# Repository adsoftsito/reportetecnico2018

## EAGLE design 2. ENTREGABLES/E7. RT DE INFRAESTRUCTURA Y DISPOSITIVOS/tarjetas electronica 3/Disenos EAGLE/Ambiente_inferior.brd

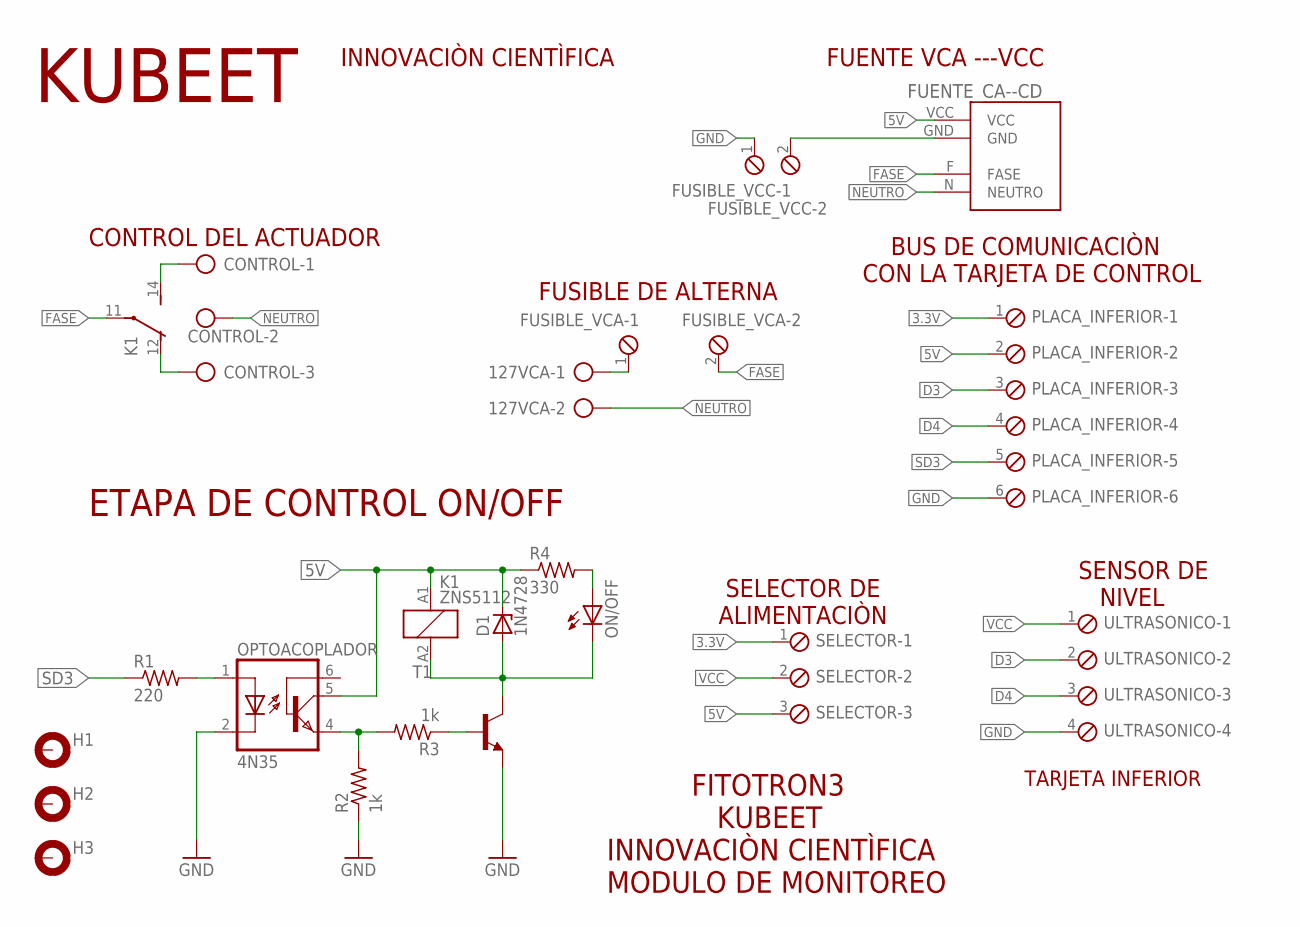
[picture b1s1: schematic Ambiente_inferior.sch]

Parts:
127VCA: AK300/2
CONTROL: AK300/3
D1: 1N4728; DO41Z10
FUENTE_CA--CD: MINI-FUENTE
FUSIBLE_VCA: MPT2; 2POL254
FUSIBLE_VCC: MPT2; 2POL254
H1, H2, H3: MOUNT-PAD-ROUND3.6; 3,6-PAD
K1: ZNS5112; ZN5
ON/OFF: LED5MM
OPTOACOPLADOR: 4N35; DIL06
PLACA_INFERIOR: MPT6; 6POL254
R1: 220; 0207/7
R2, R3: 1k; 0207/7
R4: 330; 0207/7
SELECTOR: MPT3; 3POL254
T1: 2N2222-NPN-TO92-EBC; TO92-EBC
ULTRASONICO: MPT4; 4POL254

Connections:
3.3V: PLACA_INFERIOR.1, SELECTOR.1
5V: D1.C, FUENTE_CA--CD.VCC, K1.A1 (1), OPTOACOPLADOR.5 (COL), PLACA_INFERIOR.2, R4.1, SELECTOR.3
D3: PLACA_INFERIOR.3, ULTRASONICO.2
D4: PLACA_INFERIOR.4, ULTRASONICO.3
FASE: FUENTE_CA--CD.F (FASE), FUSIBLE_VCA.2, K1.11
GND: FUSIBLE_VCC.1, OPTOACOPLADOR.2 (C), PLACA_INFERIOR.6, R2.1, T1.E, ULTRASONICO.4
unnamed: OPTOACOPLADOR.1 (A), R1.2
unnamed: D1.A, K1.A2 (2), ON/OFF.K (C), T1.C
unnamed: OPTOACOPLADOR.4 (EMI), R2.2, R3.2
unnamed: CONTROL.1, K1.14 (S)
unnamed: CONTROL.3, K1.12 (O)
unnamed: 127VCA.1, FUSIBLE_VCA.1
unnamed: R3.1, T1.B
unnamed: ON/OFF.A, R4.2
unnamed: FUENTE_CA--CD.GND, FUSIBLE_VCC.2
NEUTRO: 127VCA.2, CONTROL.2, FUENTE_CA--CD.N (NEUTRO)
SD3: PLACA_INFERIOR.5, R1.1
VCC: SELECTOR.2, ULTRASONICO.1

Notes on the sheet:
FITOTRON3 KUBEET INNOVACIÒN CIENTÌFICA MODULO DE MONITOREO
TARJETA INFERIOR
ETAPA DE CONTROL ON/OFF
FUENTE VCA ---VCC
FUSIBLE DE ALTERNA
CONTROL DEL ACTUADOR
BUS DE COMUNICACIÒN CON LA TARJETA DE CONTROL
SELECTOR DE ALIMENTACIÒN
SENSOR DE NIVEL
KUBEET
INNOVACIÒN CIENTÌFICA

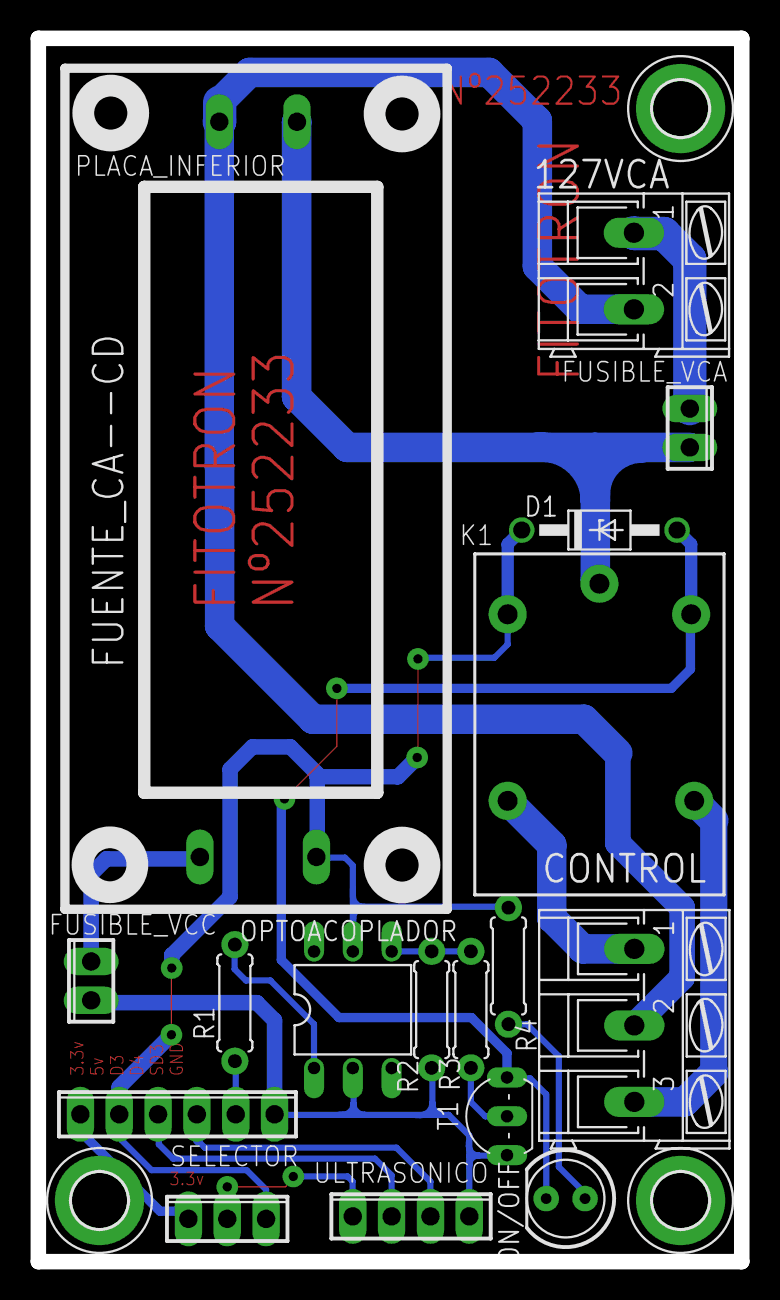
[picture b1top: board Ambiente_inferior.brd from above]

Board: 2 copper layers, 46.0 x 80.0 mm, 20 parts (0 on the bottom side), 18 nets.

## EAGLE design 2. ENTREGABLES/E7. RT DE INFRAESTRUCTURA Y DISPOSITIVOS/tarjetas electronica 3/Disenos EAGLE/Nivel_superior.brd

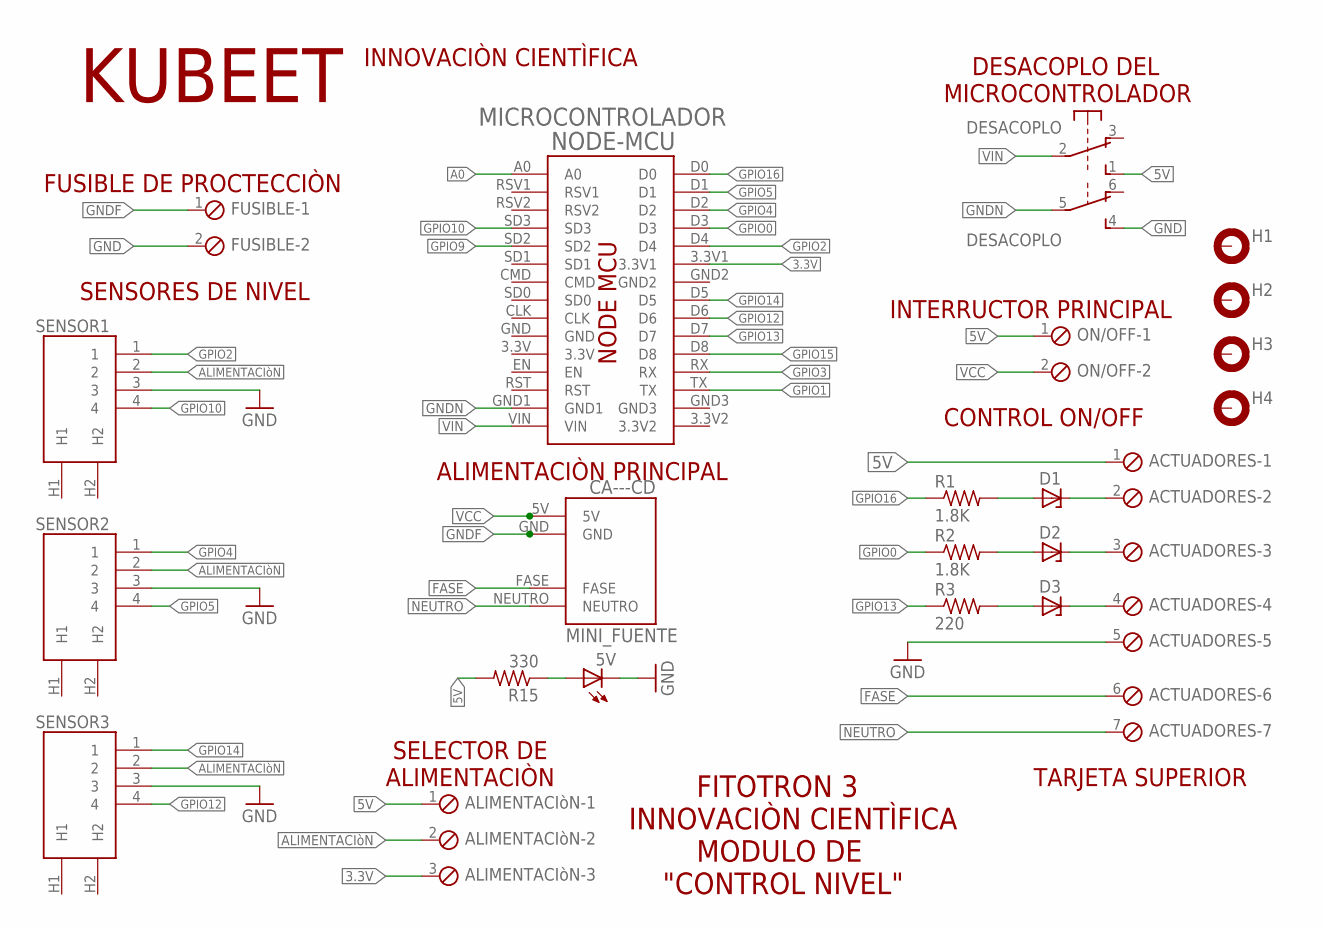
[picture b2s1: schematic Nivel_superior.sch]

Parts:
5V: LED5MM
ACTUADORES: MPT7; 7POL254
ALIMENTACIòN: MPT3; 3POL254
CA---CD: MINI_FUENTE; MINI_FUENTE2
D1, D2, D3: 1N821; DO35Z10
DESACOPLO: 9077-2
FUSIBLE: MPT2; 2POL254
H1, H2, H3, H4: MOUNT-PAD-ROUND3.6; 3,6-PAD
MICROCONTROLADOR: NODE-MCU
ON/OFF: MPT2; 2POL254
R1, R2: 1.8K; 0207/7
R3: 220; 0207/7
R15: 330; 0207/7
SENSOR1, SENSOR2, SENSOR3: RJ11

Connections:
3.3V: ALIMENTACIòN.3, MICROCONTROLADOR.3.3V1
5V: ACTUADORES.1, ALIMENTACIòN.1, DESACOPLO.1 (S), ON/OFF.1, R15.2
A0: MICROCONTROLADOR.A0
ALIMENTACIòN: ALIMENTACIòN.2, SENSOR1.2, SENSOR2.2, SENSOR3.2
FASE: ACTUADORES.6, CA---CD.FASE
GND: 5V.K (C), ACTUADORES.5, DESACOPLO.4 (S), FUSIBLE.2, SENSOR1.3, SENSOR2.3, SENSOR3.3
GNDF: CA---CD.GND, FUSIBLE.1
GNDN: DESACOPLO.5, MICROCONTROLADOR.GND1
GPIO0: MICROCONTROLADOR.D3, R2.1
GPIO1: MICROCONTROLADOR.TX
GPIO2: MICROCONTROLADOR.D4, SENSOR1.1
GPIO3: MICROCONTROLADOR.RX
GPIO4: MICROCONTROLADOR.D2, SENSOR2.1
GPIO5: MICROCONTROLADOR.D1, SENSOR2.4
GPIO9: MICROCONTROLADOR.SD2
GPIO10: MICROCONTROLADOR.SD3, SENSOR1.4
GPIO12: MICROCONTROLADOR.D6, SENSOR3.4
GPIO13: MICROCONTROLADOR.D7, R3.1
GPIO14: MICROCONTROLADOR.D5, SENSOR3.1
GPIO15: MICROCONTROLADOR.D8
GPIO16: MICROCONTROLADOR.D0, R1.1
unnamed: D1.A, R1.2
unnamed: ACTUADORES.2, D1.C
unnamed: D2.A, R2.2
unnamed: ACTUADORES.3, D2.C
unnamed: 5V.A, R15.1
unnamed: D3.A, R3.2
unnamed: ACTUADORES.4, D3.C
NEUTRO: ACTUADORES.7, CA---CD.NEUTRO
VCC: CA---CD.5V, ON/OFF.2
VIN: DESACOPLO.2, MICROCONTROLADOR.VIN

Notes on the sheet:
KUBEET
INNOVACIÒN CIENTÌFICA
FITOTRON 3 INNOVACIÒN CIENTÌFICA MODULO DE "CONTROL NIVEL"
TARJETA SUPERIOR
CONTROL ON/OFF
SENSORES DE NIVEL
DESACOPLO DEL MICROCONTROLADOR
ALIMENTACIÒN PRINCIPAL
SELECTOR DE ALIMENTACIÒN
INTERRUCTOR PRINCIPAL
FUSIBLE DE PROCTECCIÒN

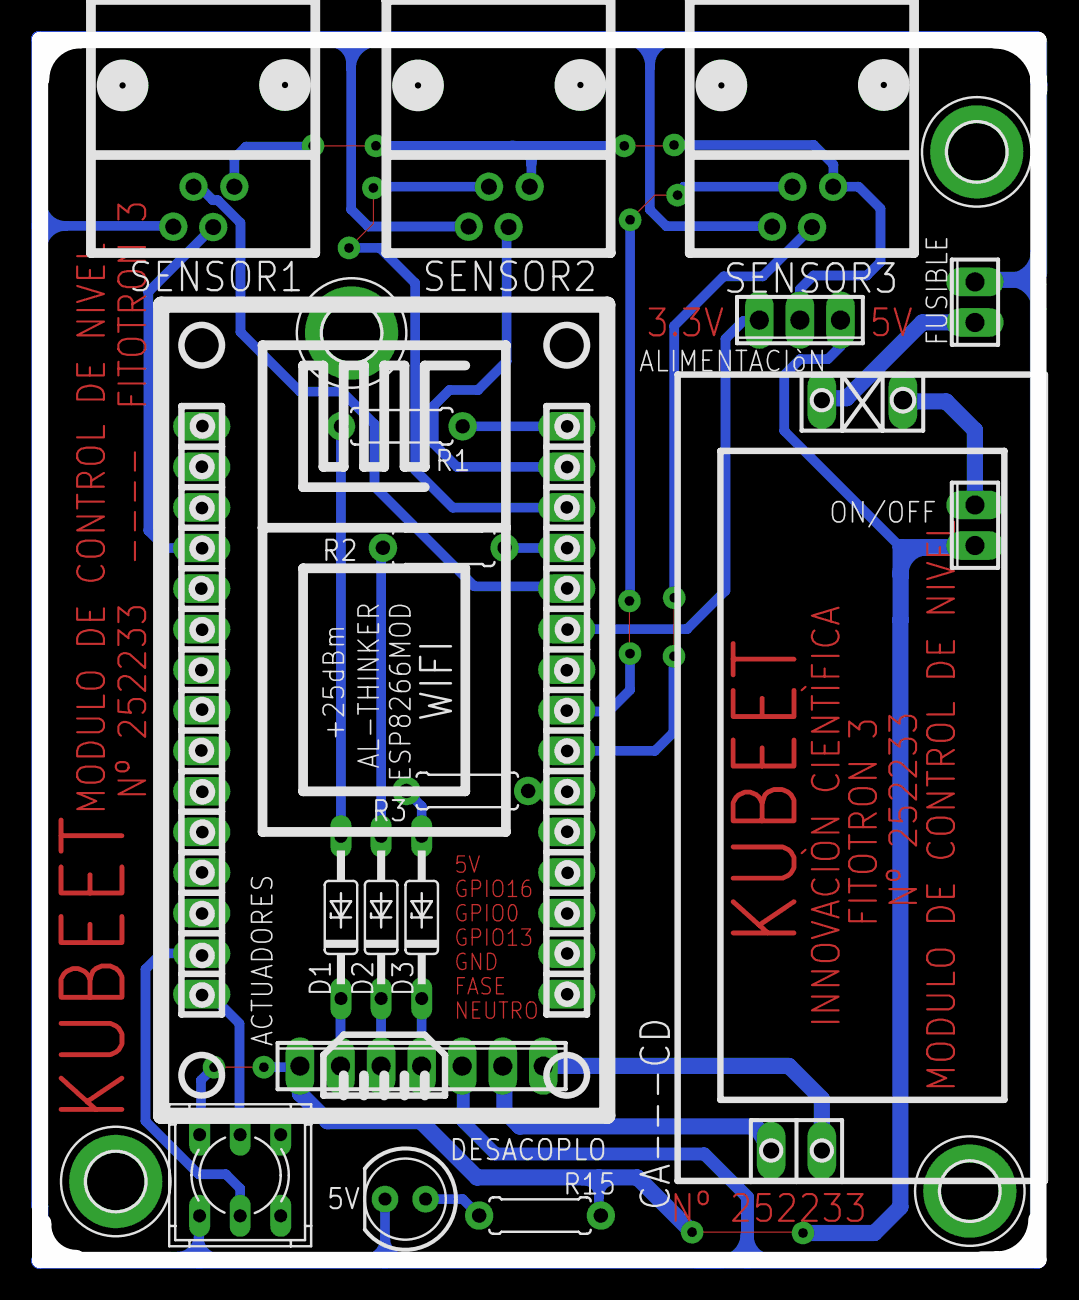
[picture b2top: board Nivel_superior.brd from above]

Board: 2 copper layers, 62.6 x 76.4 mm, 22 parts (0 on the bottom side), 26 nets.

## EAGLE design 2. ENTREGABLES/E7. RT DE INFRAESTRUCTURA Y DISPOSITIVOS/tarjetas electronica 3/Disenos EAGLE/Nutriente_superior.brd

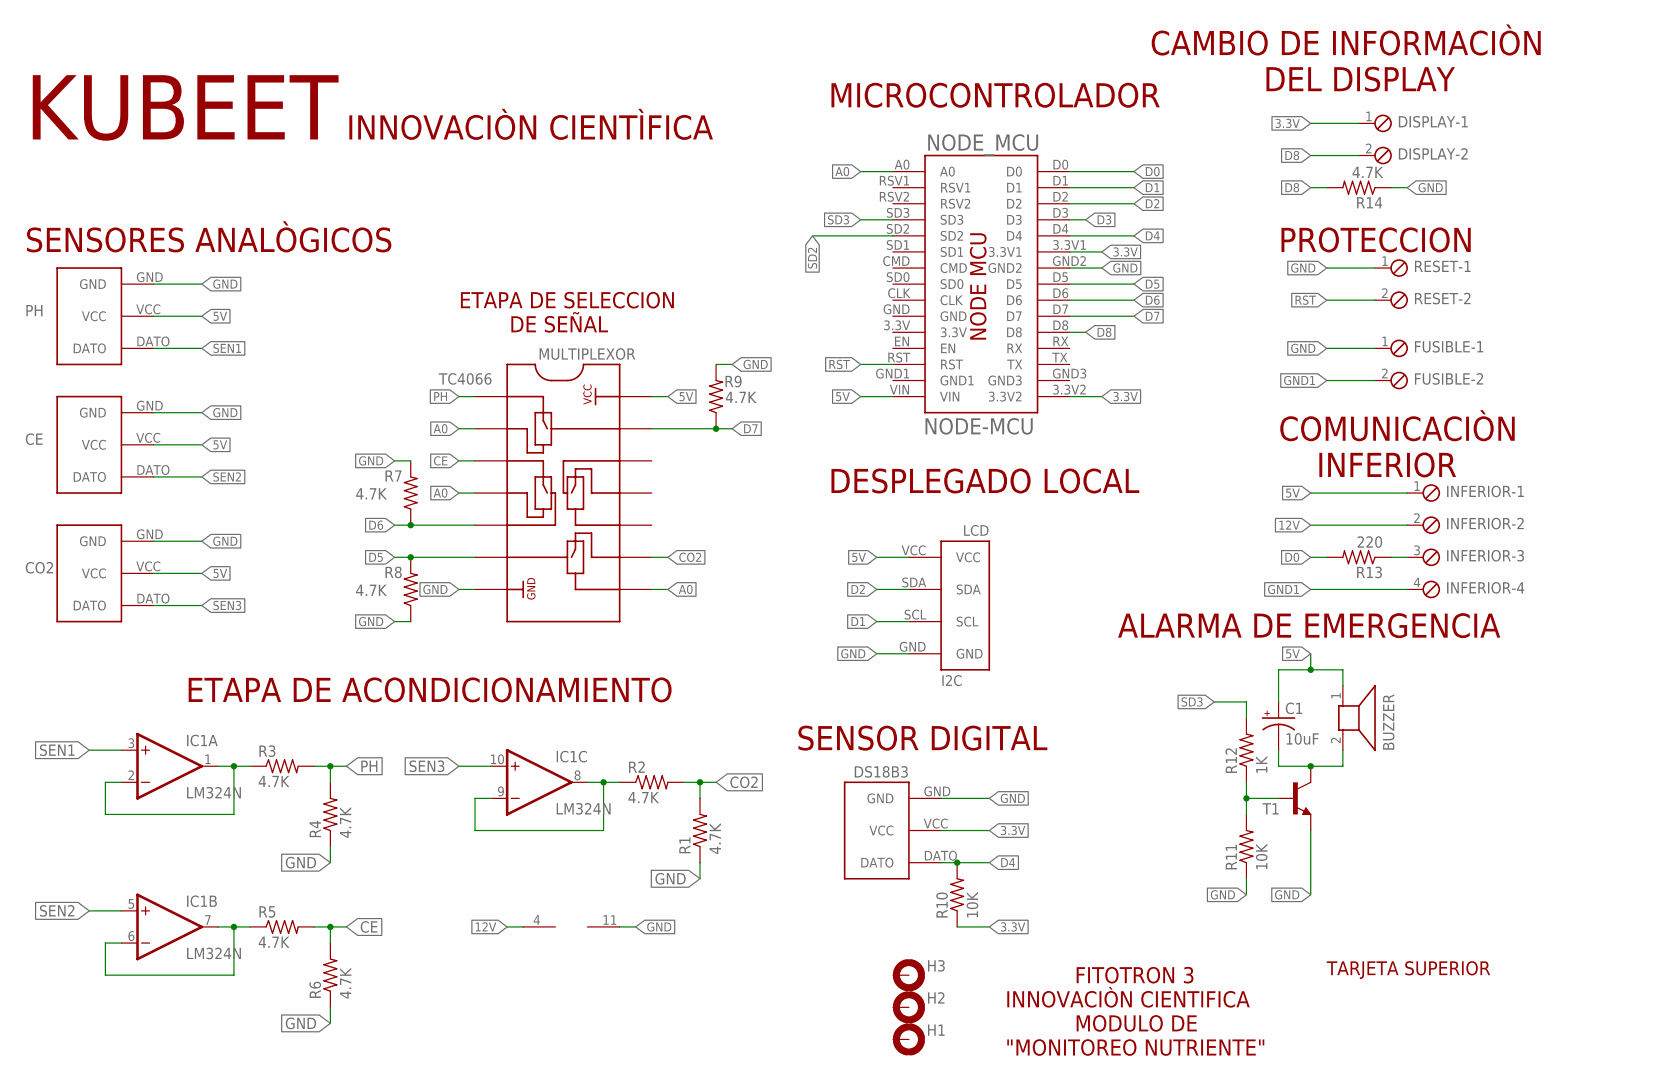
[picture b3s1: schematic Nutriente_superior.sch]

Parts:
BUZZER: AL60P
C1: 10uF; E2,5-6
CE: BASE
CO2: BASE
DISPLAY: MPT2; 2POL254
DS18B3: BASE
FUSIBLE: MPT2; 2POL254
H1, H2, H3: MOUNT-PAD-ROUND3.0; 3,0-PAD
IC1: LM324N; DIL14
INFERIOR: MPT4; 4POL254
LCD: I2C
MULTIPLEXOR: TC4066
NODE_MCU: NODE-MCU
PH: BASE
R1, R2, R3, R4, R5, R6, R7, R8, R9, R14: 4.7K; 0207/7
R10, R11: 10K; 0207/7
R12: 1K; 0207/7
R13: 220; 0207/10
RESET: MPT2; 2POL254
T1: 2N2222-NPN-TO92-EBC; TO92-EBC

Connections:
3.3V: DISPLAY.1, DS18B3.VCC, NODE_MCU.3.3V1, NODE_MCU.3.3V2, R10.1
5V: BUZZER.1, C1.+, CE.VCC, CO2.VCC, INFERIOR.1, LCD.VCC, MULTIPLEXOR.14, NODE_MCU.VIN, PH.VCC
12V: IC1.4 (V+), INFERIOR.2
A0: MULTIPLEXOR.2, MULTIPLEXOR.4, MULTIPLEXOR.8, NODE_MCU.A0
CE: MULTIPLEXOR.3, R5.2, R6.2
CO2: MULTIPLEXOR.9, R1.2, R2.2
D0: NODE_MCU.D0, R13.2
D1: LCD.SCL, NODE_MCU.D1
D2: LCD.SDA, NODE_MCU.D2
D3: NODE_MCU.D3
D4: DS18B3.DATO, NODE_MCU.D4, R10.2
D5: MULTIPLEXOR.6, NODE_MCU.D5, R8.2
D6: MULTIPLEXOR.5, NODE_MCU.D6, R7.1
D7: MULTIPLEXOR.13, NODE_MCU.D7, R9.1
D8: DISPLAY.2, NODE_MCU.D8, R14.2
GND: CE.GND, CO2.GND, DS18B3.GND, FUSIBLE.1, IC1.11 (V-), LCD.GND, MULTIPLEXOR.7, NODE_MCU.GND2, PH.GND, R1.1, R4.1, R6.1, R7.2, R8.1, R9.2, R11.1, R14.1, RESET.1, T1.E
GND1: FUSIBLE.2, INFERIOR.4
unnamed: IC1.8 (OUT), IC1.9 (-IN), R2.1
unnamed: R11.2, R12.1, T1.B
unnamed: BUZZER.2, C1.-, T1.C
unnamed: INFERIOR.3, R13.1
unnamed: IC1.1 (OUT), IC1.2 (-IN), R3.1
unnamed: IC1.6 (-IN), IC1.7 (OUT), R5.1
PH: MULTIPLEXOR.1, R3.2, R4.2
RST: NODE_MCU.RST, RESET.2
SD2: NODE_MCU.SD2
SD3: NODE_MCU.SD3, R12.2
SEN1: IC1.3 (+IN), PH.DATO
SEN2: CE.DATO, IC1.5 (+IN)
SEN3: CO2.DATO, IC1.10 (+IN)

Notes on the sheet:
KUBEET
INNOVACIÒN CIENTÌFICA
SENSOR DIGITAL
FITOTRON 3 INNOVACIÒN CIENTIFICA MODULO DE "MONITOREO NUTRIENTE"
TARJETA SUPERIOR
MICROCONTROLADOR
DESPLEGADO LOCAL
ETAPA DE ACONDICIONAMIENTO
ETAPA DE SELECCION DE SEÑAL
SENSORES ANALÒGICOS
CAMBIO DE INFORMACIÒN DEL DISPLAY
COMUNICACIÒN INFERIOR
PROTECCION
ALARMA DE EMERGENCIA

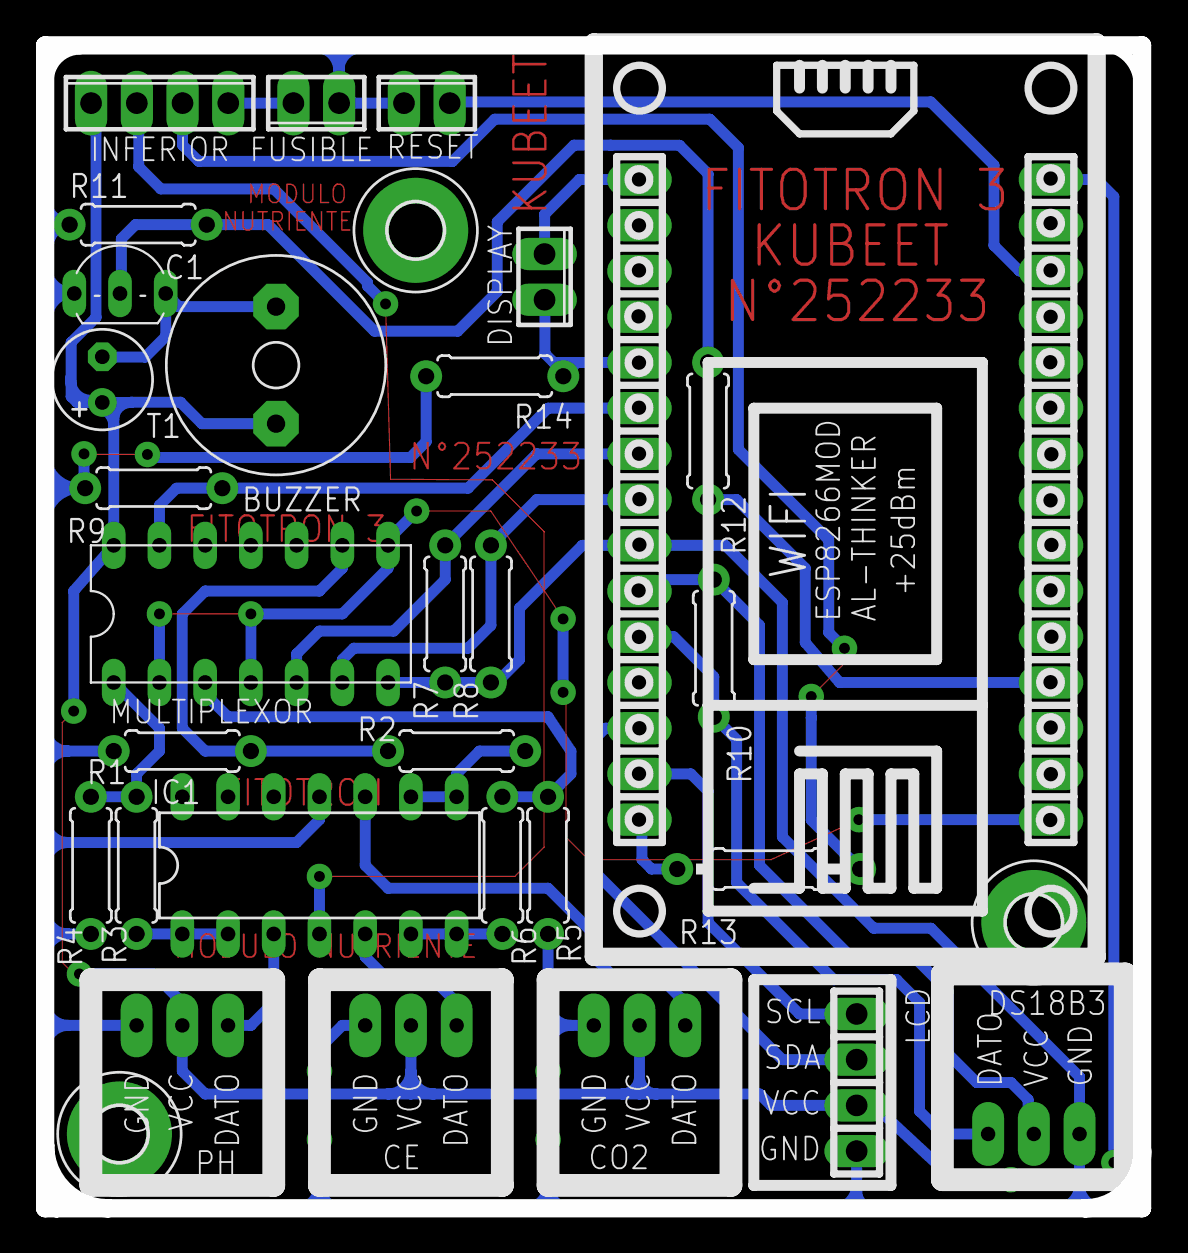
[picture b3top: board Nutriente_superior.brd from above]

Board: 2 copper layers, 61.0 x 64.6 mm, 32 parts (0 on the bottom side), 28 nets.

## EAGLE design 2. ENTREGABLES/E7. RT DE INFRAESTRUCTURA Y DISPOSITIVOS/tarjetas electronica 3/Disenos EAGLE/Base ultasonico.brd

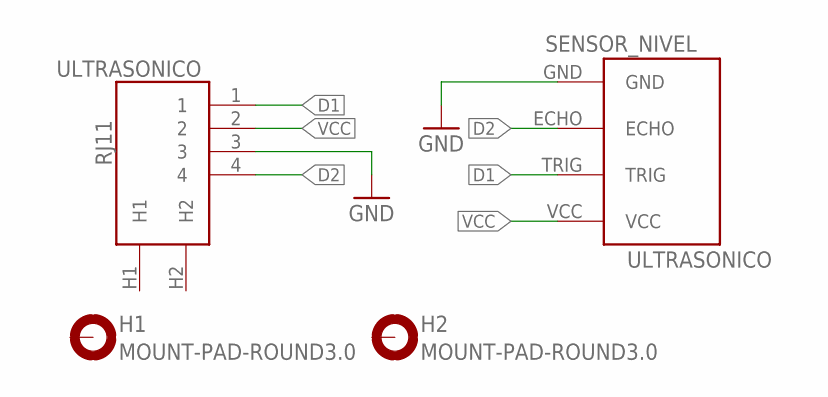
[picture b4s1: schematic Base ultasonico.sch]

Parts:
H1, H2: MOUNT-PAD-ROUND3.0; 3,0-PAD
SENSOR_NIVEL: ULTRASONICO
ULTRASONICO: RJ11

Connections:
D1: SENSOR_NIVEL.TRIG, ULTRASONICO.1
D2: SENSOR_NIVEL.ECHO, ULTRASONICO.4
GND: SENSOR_NIVEL.GND, ULTRASONICO.3
VCC: SENSOR_NIVEL.VCC, ULTRASONICO.2

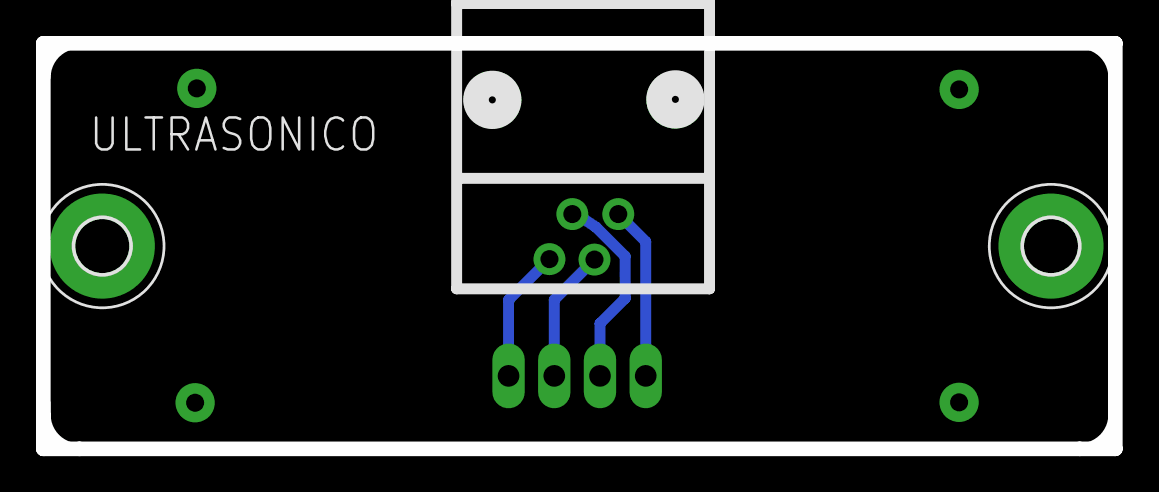
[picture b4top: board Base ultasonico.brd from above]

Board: 2 copper layers, 59.6 x 22.5 mm, 4 parts (1 on the bottom side), 4 nets.

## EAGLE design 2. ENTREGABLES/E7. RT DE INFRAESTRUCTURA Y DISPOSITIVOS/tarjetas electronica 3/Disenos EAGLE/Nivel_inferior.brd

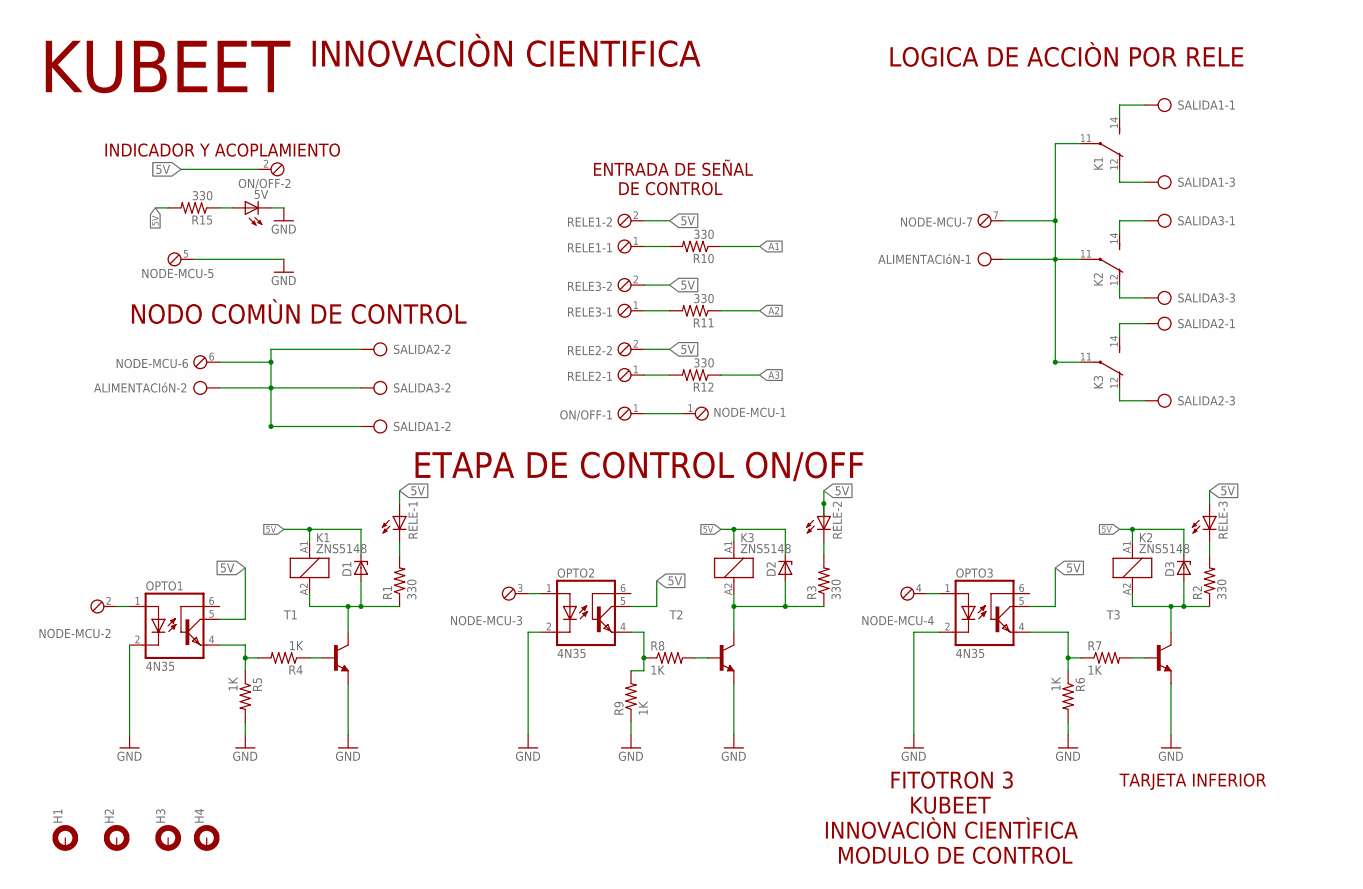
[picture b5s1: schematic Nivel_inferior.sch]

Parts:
5V: LED5MM
ALIMENTACIóN: AK300/2
D1, D2, D3: 1N821; DO35Z10
H1, H2, H3, H4: MOUNT-PAD-ROUND3.6; 3,6-PAD
K1, K2, K3: ZNS5148; ZN5
NODE-MCU: MPT7; 7POL254
ON/OFF: MPT2; 2POL254
OPTO1, OPTO2, OPTO3: 4N35; DIL06
R1, R2, R3, R10, R11, R12, R15: 330; 0207/7
R4, R5, R6, R7, R8, R9: 1K; 0207/7
RELE1, RELE2, RELE3: MPT2; 2POL254
RELE-1, RELE-2, RELE-3: LED5MM
SALIDA1, SALIDA2, SALIDA3: AK300/3
T1, T2, T3: 2N2222-NPN-TO92-EBC; TO92-EBC

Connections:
5V: D1.C, D2.C, D3.C, K1.A1 (1), K2.A1 (1), K3.A1 (1), ON/OFF.2, OPTO1.5 (COL), OPTO2.5 (COL), OPTO3.5 (COL), R15.2, RELE1.2, RELE2.2, RELE3.2, RELE-1.A, RELE-2.A, RELE-3.A
A: ALIMENTACIóN.1, K1.11, K2.11, K3.11, NODE-MCU.7
A1: NODE-MCU.2, OPTO1.1 (A), R10.1
A2: NODE-MCU.4, OPTO3.1 (A), R11.1
A3: NODE-MCU.3, OPTO2.1 (A), R12.1
GND: 5V.K (C), NODE-MCU.5, OPTO1.2 (C), OPTO2.2 (C), OPTO3.2 (C), R5.2, R6.2, R9.1, T1.E, T2.E, T3.E
unnamed: ALIMENTACIóN.2, NODE-MCU.6, SALIDA1.2, SALIDA2.2, SALIDA3.2
unnamed: K1.14 (S), SALIDA1.1
unnamed: K1.12 (O), SALIDA1.3
unnamed: K2.14 (S), SALIDA3.1
unnamed: K2.12 (O), SALIDA3.3
unnamed: K3.14 (S), SALIDA2.1
unnamed: K3.12 (O), SALIDA2.3
unnamed: NODE-MCU.1, ON/OFF.1
unnamed: D1.A, K1.A2 (2), R1.1, T1.C
unnamed: D3.A, K2.A2 (2), R2.1, T3.C
unnamed: 5V.A, R15.1
unnamed: D2.A, K3.A2 (2), R3.1, T2.C
unnamed: R12.2, RELE2.1
unnamed: R1.2, RELE-1.K (C)
unnamed: R2.2, RELE-3.K (C)
unnamed: R3.2, RELE-2.K (C)
unnamed: R7.2, T3.B
unnamed: R4.1, T1.B
unnamed: OPTO1.4 (EMI), R4.2, R5.1
unnamed: OPTO3.4 (EMI), R6.1, R7.1
unnamed: R8.2, T2.B
unnamed: OPTO2.4 (EMI), R8.1, R9.2
unnamed: R11.2, RELE3.1
unnamed: R10.2, RELE1.1

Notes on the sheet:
KUBEET
ETAPA DE CONTROL ON/OFF
ENTRADA DE SEÑAL DE CONTROL
LOGICA DE ACCIÒN POR RELE
NODO COMÙN DE CONTROL
INDICADOR Y ACOPLAMIENTO
INNOVACIÒN CIENTIFICA
FITOTRON 3 KUBEET INNOVACIÒN CIENTÌFICA MODULO DE CONTROL
TARJETA INFERIOR

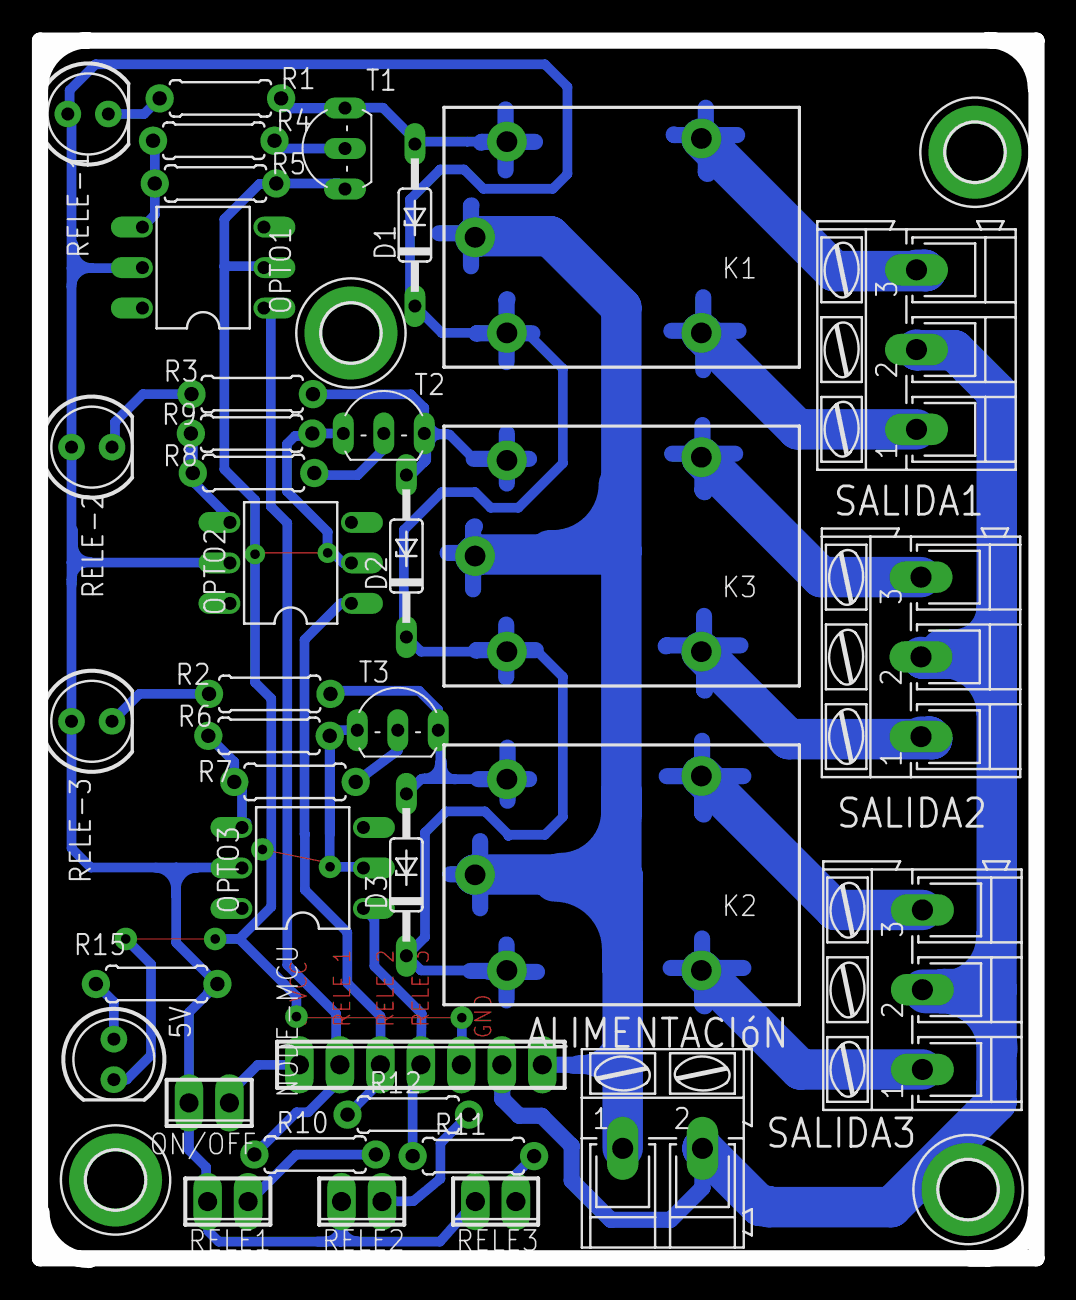
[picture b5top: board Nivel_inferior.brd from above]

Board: 2 copper layers, 62.5 x 76.5 mm, 42 parts (0 on the bottom side), 30 nets.

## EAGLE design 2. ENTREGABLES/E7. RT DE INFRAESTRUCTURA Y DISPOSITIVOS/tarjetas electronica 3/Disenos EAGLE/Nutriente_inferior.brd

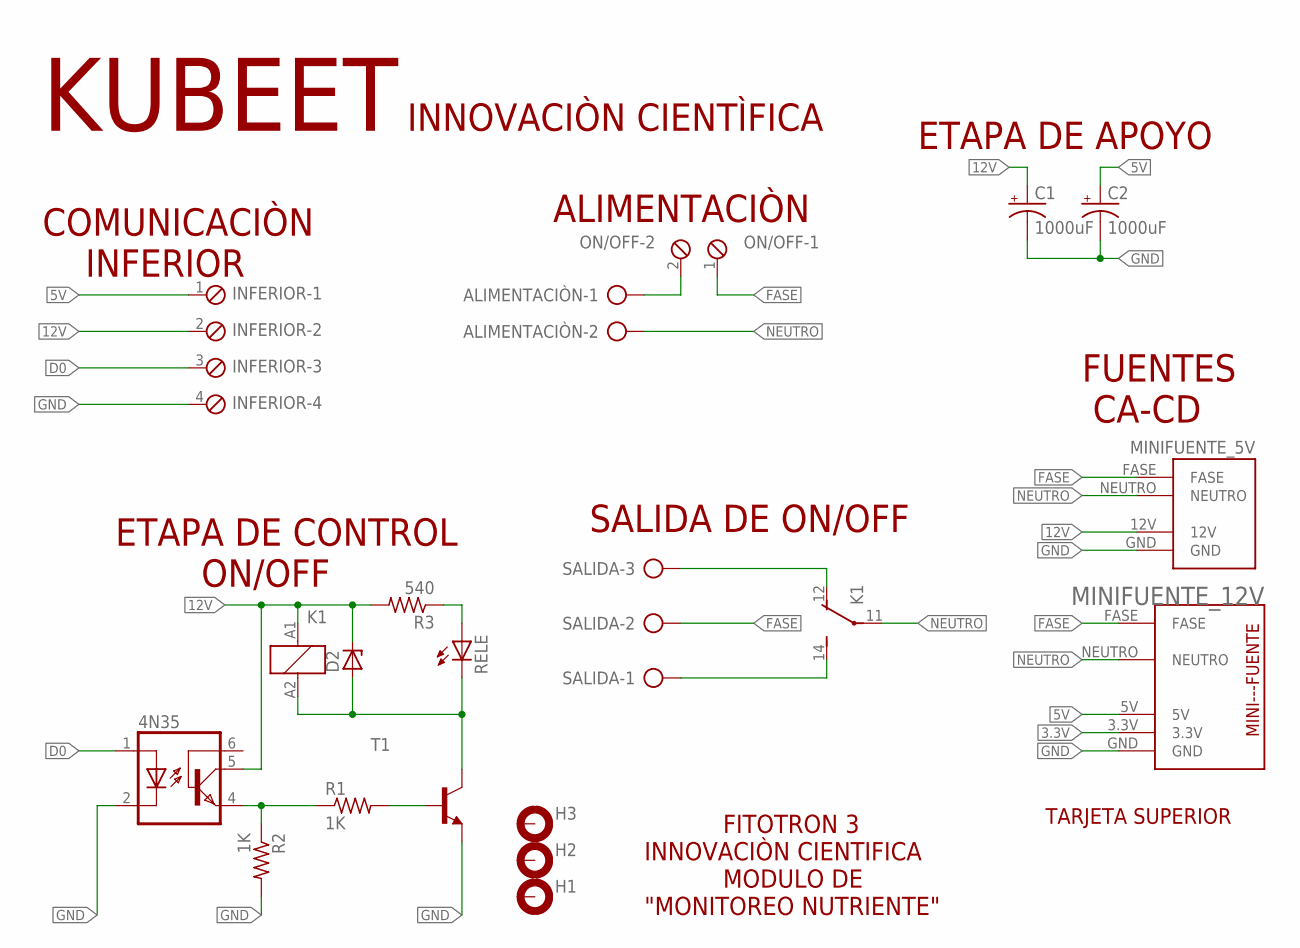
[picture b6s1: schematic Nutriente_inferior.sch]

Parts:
4N35: 4N35; DIL06
ALIMENTACIÒN: AK300/2
C1, C2: 1000uF; E3,5-10
D2: 1N821; DO35Z10
H1, H2, H3: MOUNT-PAD-ROUND3.0; 3,0-PAD
INFERIOR: MPT4; 4POL254
K1: ZNS5112; ZN5
MINIFUENTE_5V: MINIFUENTE4
MINIFUENTE_12V: MINIFUENTE3
ON/OFF: MPT2; 2POL254
R1, R2: 1K; 0207/7
R3: 540; 0207/7
RELE: LED5MM
SALIDA: AK300/3
T1: 2N2222-NPN-TO92-EBC; TO92-EBC

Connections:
3.3V: MINIFUENTE_12V.3.3V
5V: C2.+, INFERIOR.1, MINIFUENTE_12V.5V
12V: 4N35.5 (COL), C1.+, D2.C, INFERIOR.2, K1.A1 (1), MINIFUENTE_5V.12V, R3.2
D0: 4N35.1 (A), INFERIOR.3
FASE: MINIFUENTE_5V.FASE, MINIFUENTE_12V.FASE, ON/OFF.1, SALIDA.2
GND: 4N35.2 (C), C1.-, C2.-, INFERIOR.4, MINIFUENTE_5V.GND, MINIFUENTE_12V.GND, R2.2, T1.E
unnamed: ALIMENTACIÒN.1, ON/OFF.2
unnamed: 4N35.4 (EMI), R1.1, R2.1
unnamed: R1.2, T1.B
unnamed: R3.1, RELE.A
unnamed: D2.A, K1.A2 (2), RELE.K (C), T1.C
unnamed: K1.12 (O), SALIDA.3
unnamed: K1.14 (S), SALIDA.1
NEUTRO: ALIMENTACIÒN.2, K1.11, MINIFUENTE_5V.NEUTRO, MINIFUENTE_12V.NEUTRO

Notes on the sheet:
KUBEET
INNOVACIÒN CIENTÌFICA
FITOTRON 3 INNOVACIÒN CIENTIFICA MODULO DE "MONITOREO NUTRIENTE"
TARJETA SUPERIOR
COMUNICACIÒN INFERIOR
ETAPA DE CONTROL ON/OFF
SALIDA DE ON/OFF
FUENTES CA-CD
ALIMENTACIÒN
ETAPA DE APOYO

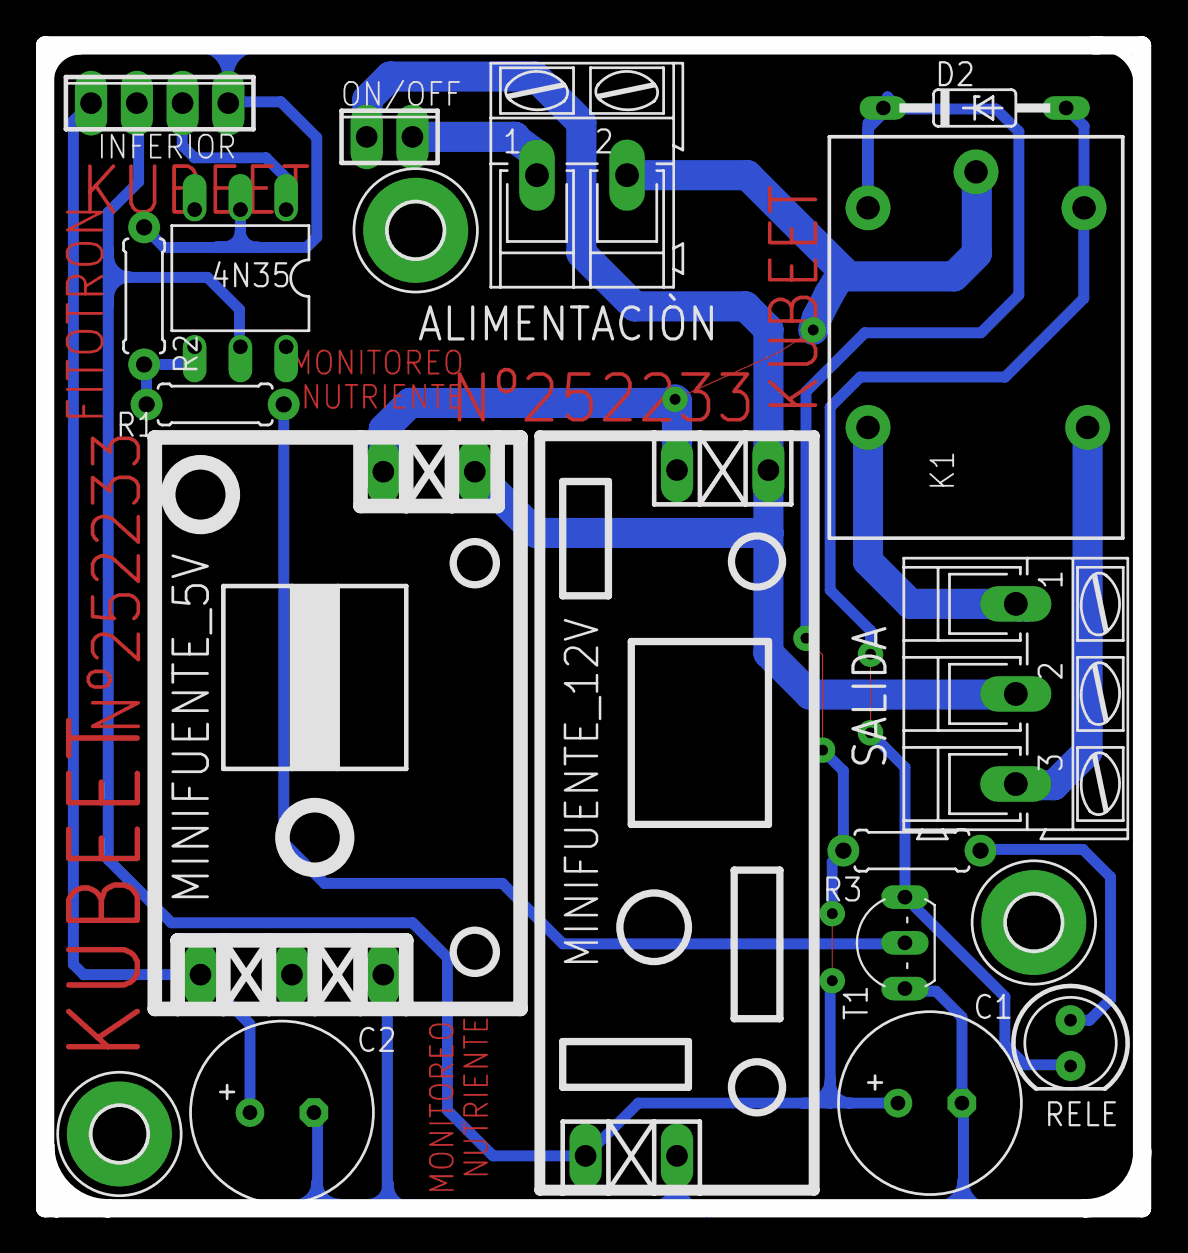
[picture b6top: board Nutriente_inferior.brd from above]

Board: 2 copper layers, 61.0 x 64.6 mm, 19 parts (0 on the bottom side), 13 nets.

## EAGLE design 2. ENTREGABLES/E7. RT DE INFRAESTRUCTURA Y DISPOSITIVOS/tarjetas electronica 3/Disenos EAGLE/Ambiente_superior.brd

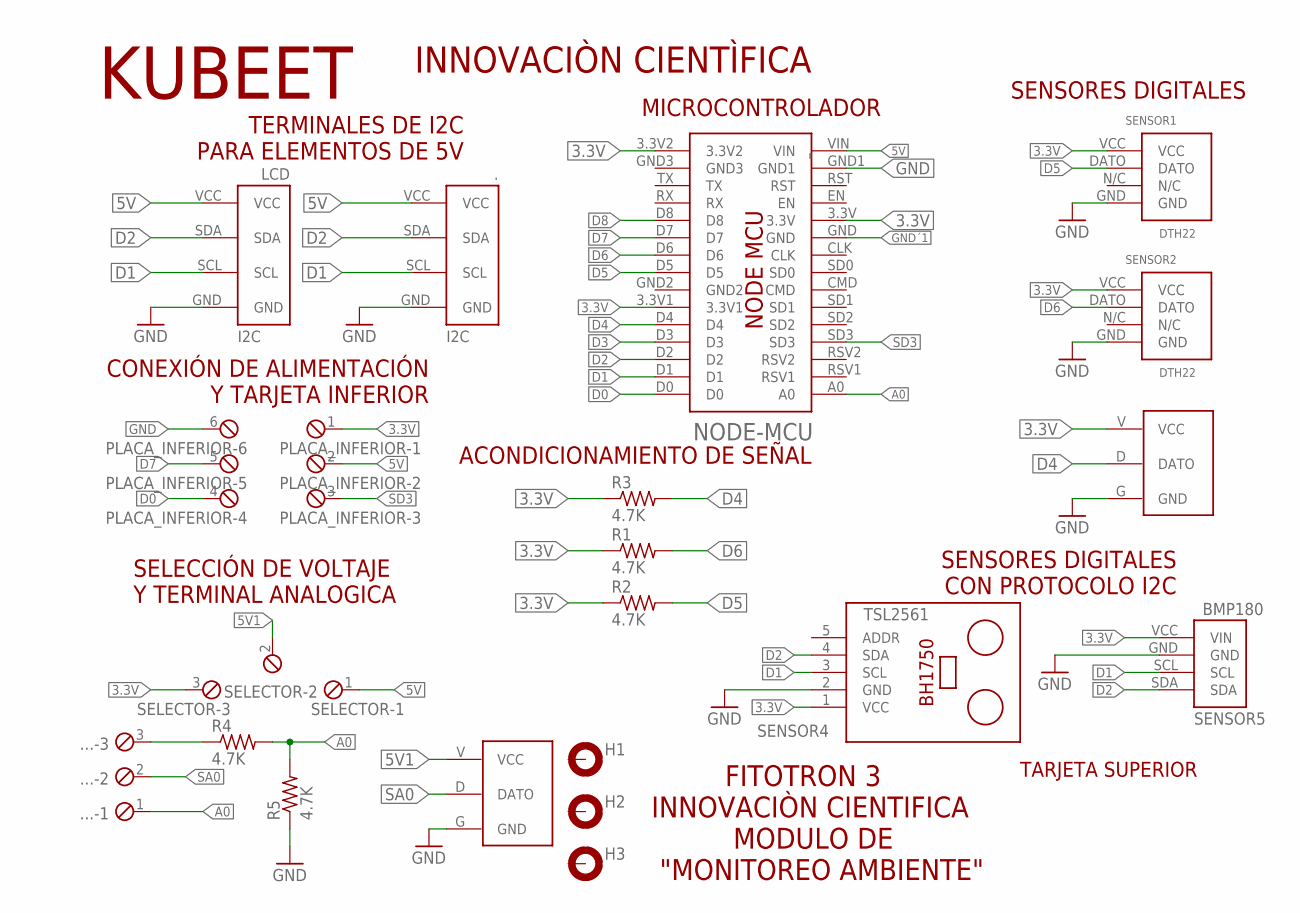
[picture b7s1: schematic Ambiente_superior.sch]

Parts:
-: NODE-MCU
.: I2C
..: LM35
...: MPT3; 3POL254
H1, H2, H3: MOUNT-PAD-ROUND3.6; 3,6-PAD
LCD: I2C
PLACA_INFERIOR: MPT6; 6POL254
R1, R2, R3, R4, R5: 4.7K; 0207/7
SELECTOR: MPT3; 3POL254
SENSOR1, SENSOR2: DTH22
SENSOR3: DS18B20; LM35
SENSOR4: TSL2561; LIGHT-SENSOR-BH1750
SENSOR5: BMP180

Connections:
3.3V: -.3.3V, -.3.3V1, -.3.3V2, PLACA_INFERIOR.1, R1.1, R2.1, R3.1, SELECTOR.3, SENSOR1.VCC, SENSOR2.VCC, SENSOR3.V (VCC), SENSOR4.1 (VCC), SENSOR5.VCC (VIN)
5V: -.VIN, ..VCC, LCD.VCC, PLACA_INFERIOR.2, SELECTOR.1
5V1: ...V (VCC), SELECTOR.2
A0: -.A0, ....1, R4.2, R5.2
D0: -.D0, PLACA_INFERIOR.4
D1: -.D1, ..SCL, LCD.SCL, SENSOR4.3 (SCL), SENSOR5.SCL
D2: -.D2, ..SDA, LCD.SDA, SENSOR4.4 (SDA), SENSOR5.SDA
D3: -.D3
D4: -.D4, R3.2, SENSOR3.D (DATO)
D5: -.D5, R2.2, SENSOR1.DATO
D6: -.D6, R1.2, SENSOR2.DATO
D7: -.D7, PLACA_INFERIOR.5
D8: -.D8
GND: -.GND1, ..GND, ...G (GND), LCD.GND, PLACA_INFERIOR.6, R5.1, SENSOR1.GND, SENSOR2.GND, SENSOR3.G (GND), SENSOR4.2 (GND), SENSOR5.GND
GND´1: -.GND
unnamed: ....3, R4.1
SA0: ...D (DATO), ....2
SD3: -.SD3, PLACA_INFERIOR.3

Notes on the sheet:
FITOTRON 3 INNOVACIÒN CIENTIFICA MODULO DE "MONITOREO AMBIENTE"
TARJETA SUPERIOR
TERMINALES DE I2C PARA ELEMENTOS DE 5V
MICROCONTROLADOR
SENSORES DIGITALES
SELECCIÓN DE VOLTAJE Y TERMINAL ANALOGICA
CONEXIÓN DE ALIMENTACIÓN Y TARJETA INFERIOR
ACONDICIONAMIENTO DE SEÑAL
SENSORES DIGITALES CON PROTOCOLO I2C
KUBEET
INNOVACIÒN CIENTÌFICA

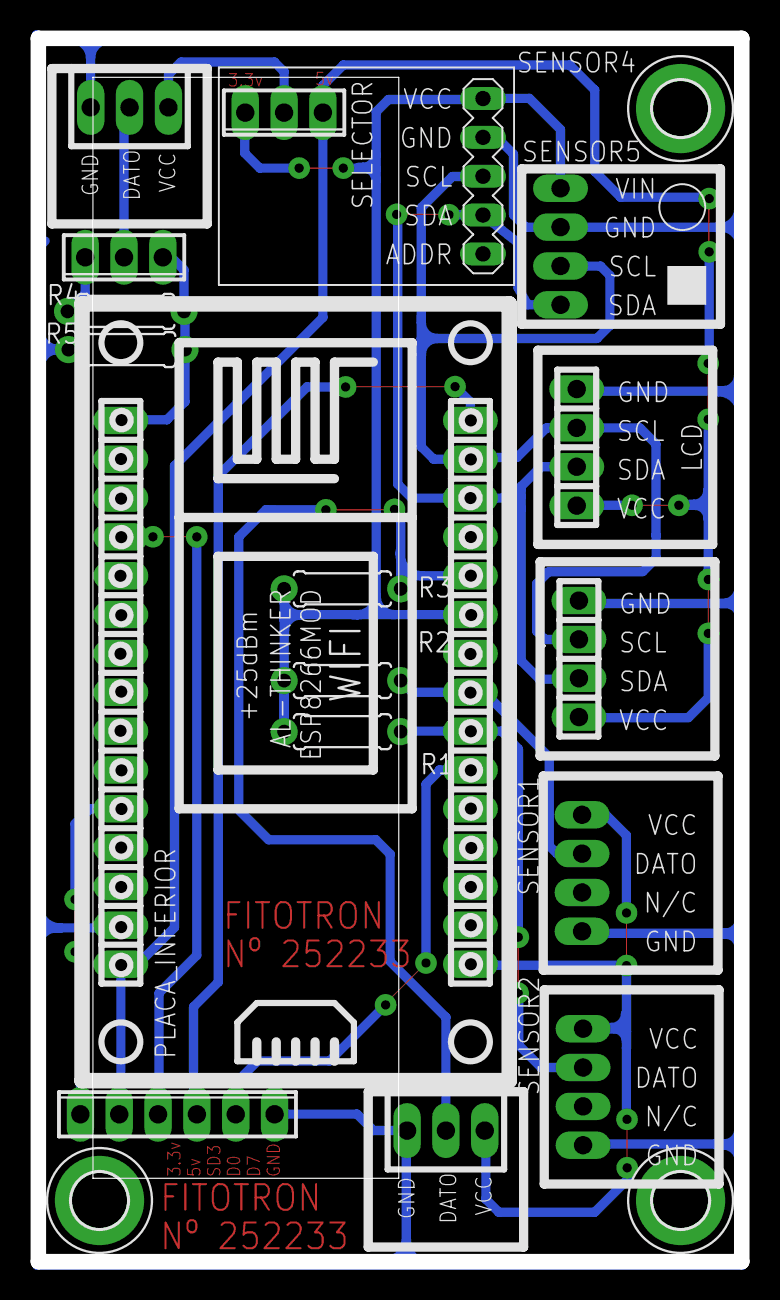
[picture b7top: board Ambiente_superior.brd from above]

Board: 2 copper layers, 46.0 x 80.0 mm, 20 parts (0 on the bottom side), 15 nets.

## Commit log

2019-01-21 rep 2018

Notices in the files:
parts and their libraries:
Modulos: Released under the Creative Commons Attribution 4.0 International License: http://creativecommons.org/licenses/by/4.0
SparkFun-Aesthetics: Licensing: Creative Commons ShareAlike 4.0 International - https://creativecommons.org/licenses/by-sa/4.0
